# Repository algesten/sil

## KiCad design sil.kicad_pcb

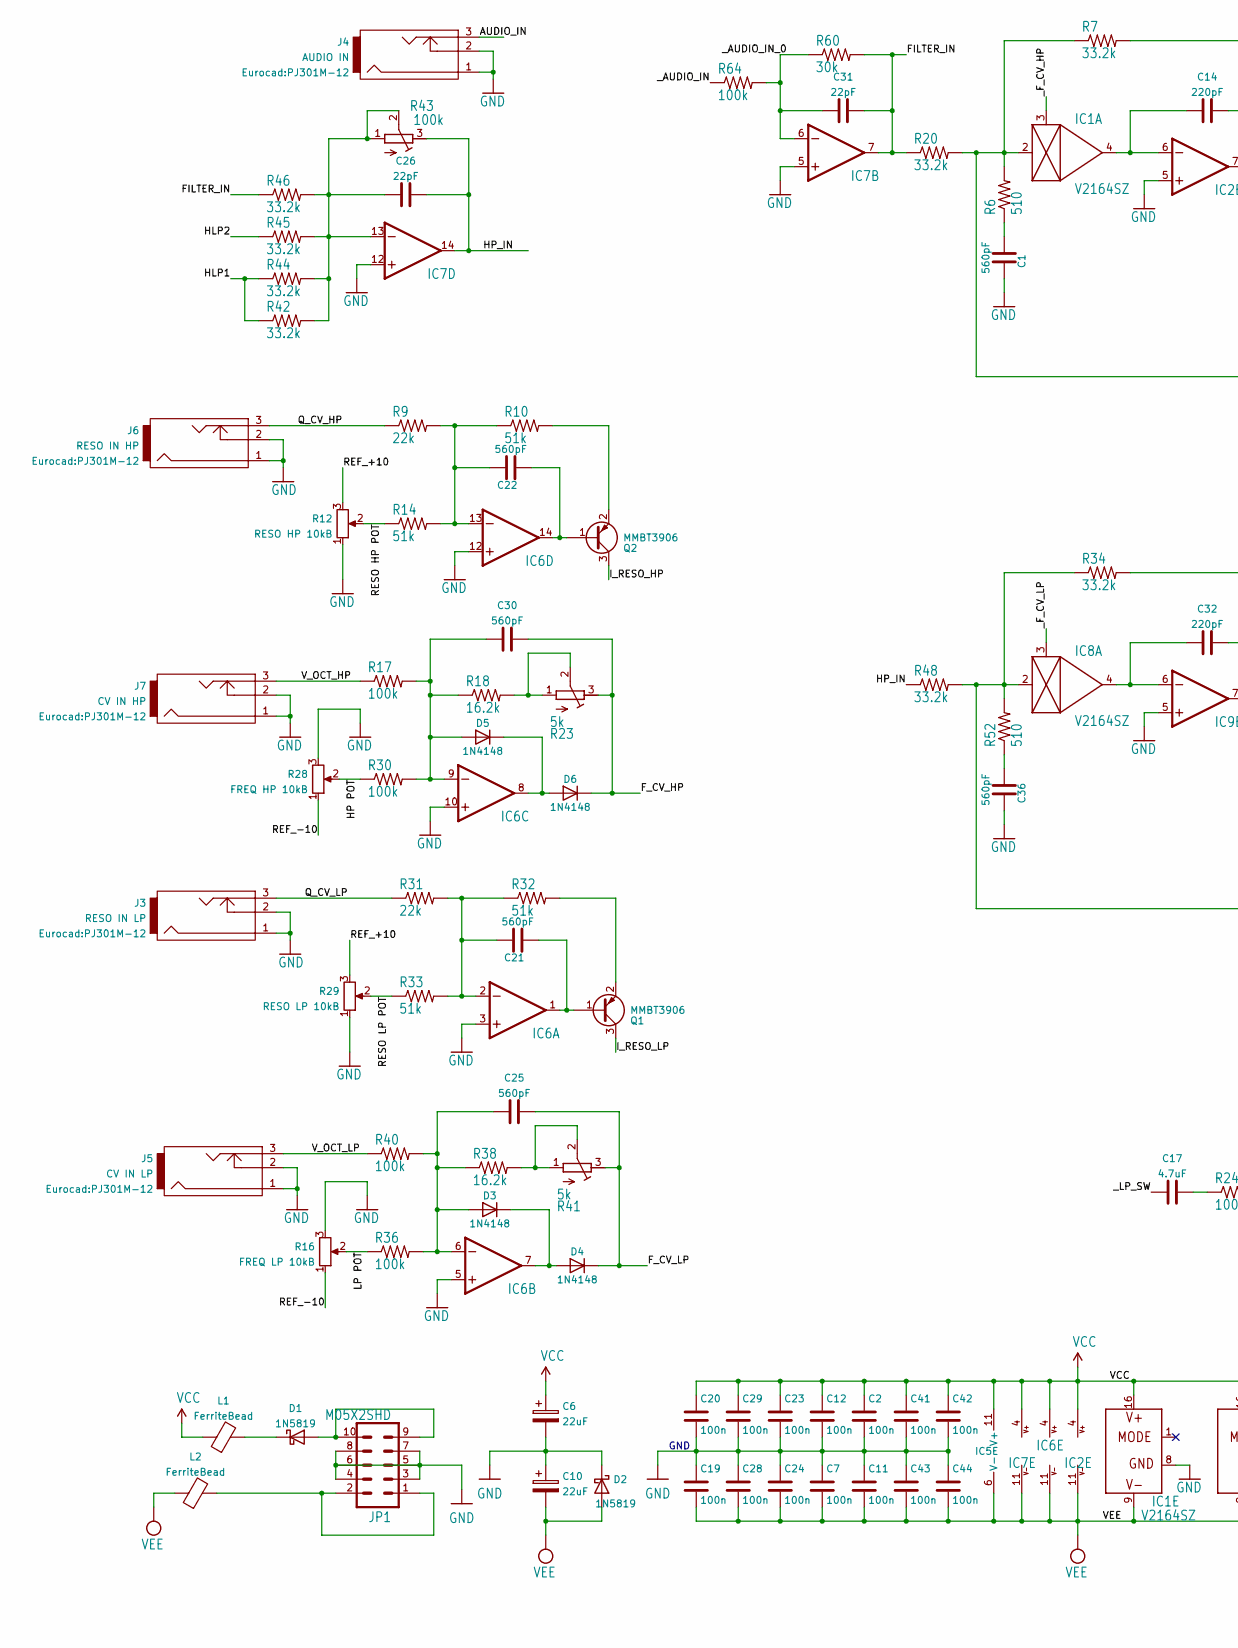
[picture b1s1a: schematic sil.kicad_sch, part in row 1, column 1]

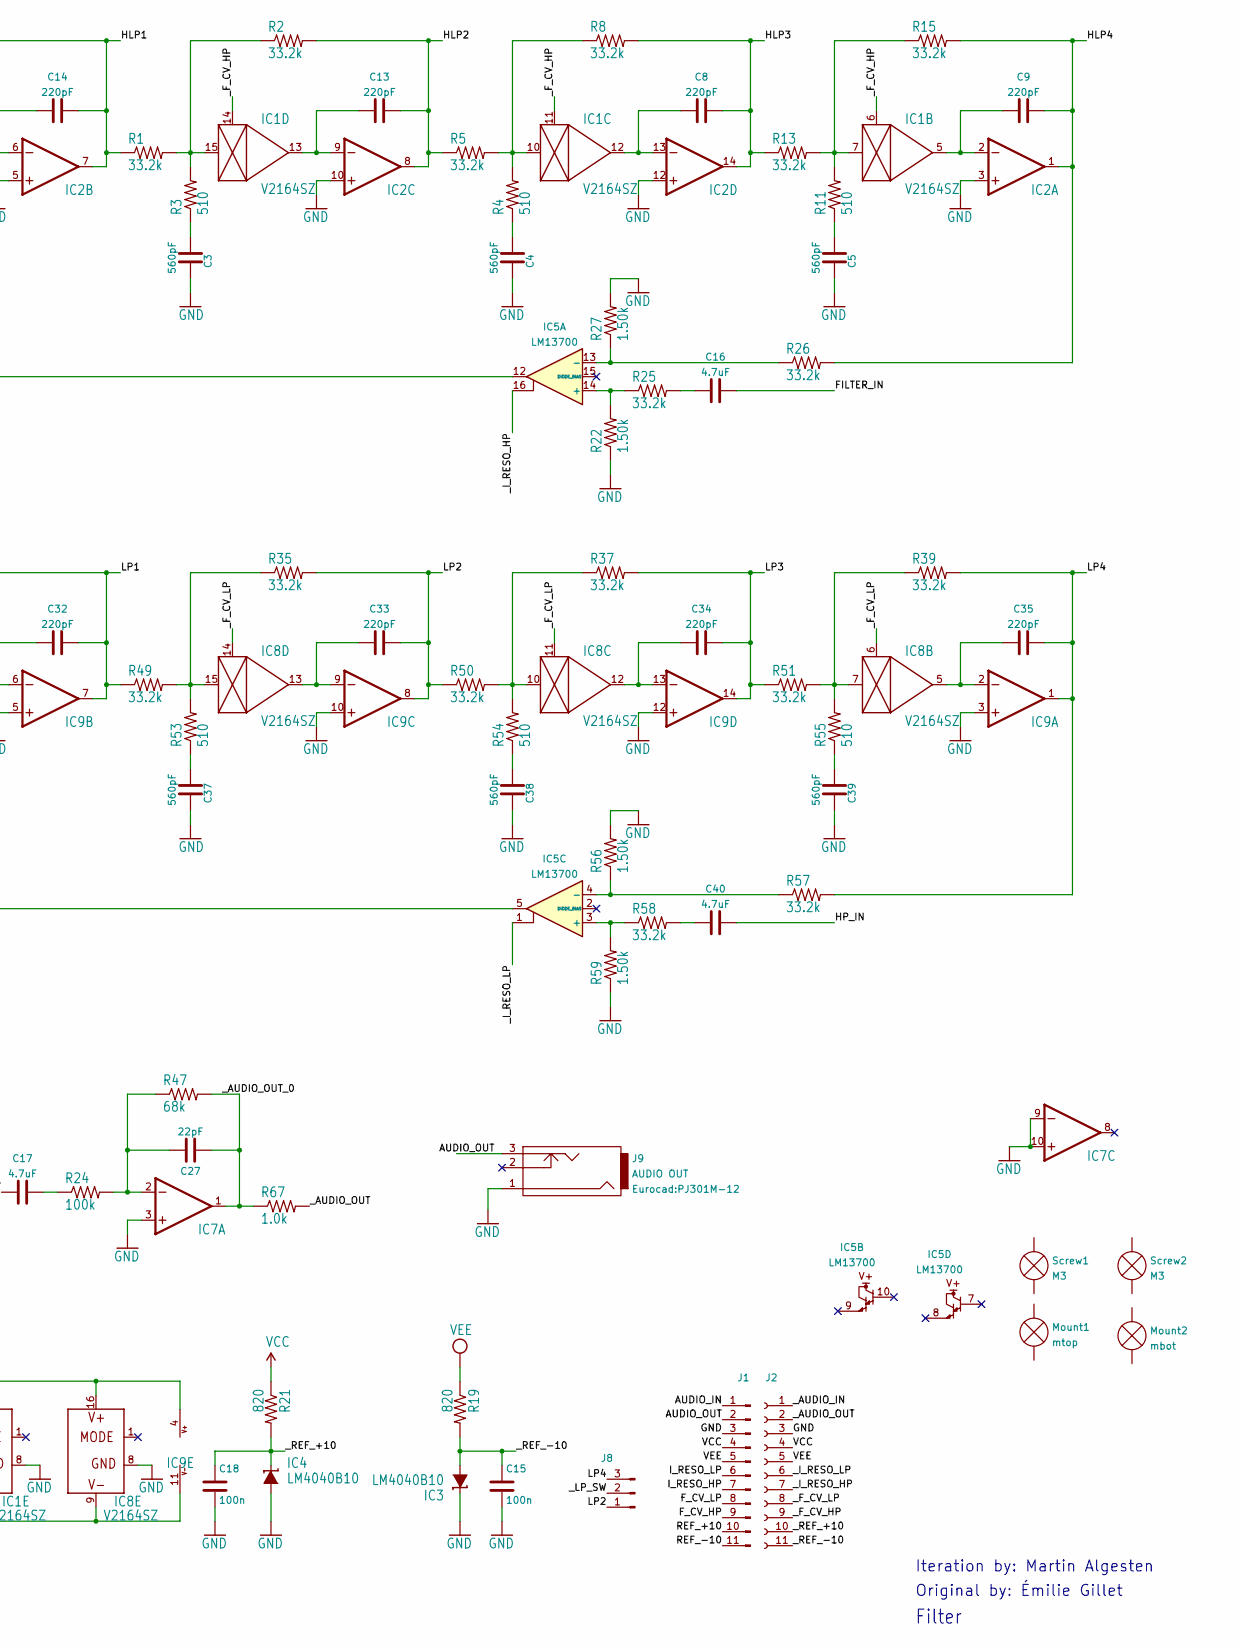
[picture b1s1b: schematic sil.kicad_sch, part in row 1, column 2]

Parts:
C1, C3, C4, C5, C21, C22, C25, C30, C36, C37, C38, C39: 560pF; C_0402_1005Metric; LCSC C318606
C2, C7, C11, C12, C15, C18, C19, C20, C23, C24, C28, C29, C41, C42, C43, C44: 100n; C_0402_1005Metric; LCSC C105882
C6, C10: 22uF; CP_Elec_5x5.4; LCSC C239256
C8, C9, C13, C14, C32, C33, C34, C35: 220pF; R_0603_1608Metric; LCSC C302060
C16, C40: 4.7uF; C_1206_3216Metric; LCSC C7237
C17: 4.7uF; R_1206_3216Metric; LCSC C318753
C26, C27, C31: 22pF; C_0402_1005Metric; LCSC C1555
D1, D2: 1N5819; D_SOD-123; LCSC C2905649
D3, D4, D5, D6: 1N4148; D_SOD-523; LCSC C68948
IC1, IC8: V2164SZ; SOIC-16_4.55x10.3mm_P1.27mm
IC2, IC7, IC9: OPA1679; TSSOP-14_4.4x5mm_P0.65mm
IC3, IC4: LM4040B10; SOT-23; LCSC C201738
IC5: LM13700; SOIC-16_3.9x9.9mm_P1.27mm
IC6: TL074; TSSOP-14_4.4x5mm_P0.65mm
J1: Conn_01x11_Male; PinHeader_1x11_P2.54mm_Vertical
J2: Conn_01x08_Female; PinSocket_1x11_P2.54mm_Vertical
J3: RESO IN LP; PJ301M-12
J4: AUDIO IN; PJ301M-12
J5: CV IN LP; PJ301M-12
J6: RESO IN HP; PJ301M-12
J7: CV IN HP; PJ301M-12
J8: Conn_01x03_Male; PinHeader_1x03_P2.54mm_Vertical
J9: AUDIO OUT; PJ301M-12
JP1: M05X2SHD; Power_small
L1, L2: FerriteBead; R_0402_1005Metric; LCSC C76883
Mount1: mtop; Mounting hole
Mount2: mbot; Mounting hole
Q1, Q2: MMBT3906; SOT-523; LCSC C2828444
R1, R2, R5, R7, R8, R13, R15, R20, R25, R26, R34, R35, R37, R39, R42, R44, R45, R46, R48, R49, R50, R51, R57, R58: 33.2k; R_0402_1005Metric; LCSC C2692992
R3, R4, R6, R11, R52, R53, R54, R55: 510; R_0402_1005Metric; LCSC C25123
R9, R31: 22k; R_0402_1005Metric; LCSC C25768
R10, R14, R32, R33: 51k; R_0402_1005Metric; LCSC C25794
R12: RESO HP 10kB; Alpha9mmPot
R16: FREQ LP 10kB; Alpha9mmPot
R17, R24, R30, R36, R40, R64: 100k; R_0402_1005Metric; LCSC C25741
R18, R38: 16.2k; R_0402_1005Metric; LCSC C27176
R19, R21: 820; R_0402_1005Metric; LCSC C227240
R22, R27, R56, R59: 1.50k; R_0402_1005Metric; LCSC C2692761
R23, R41: 5k; bourns trimpot
R28: FREQ HP 10kB; Alpha9mmPot
R29: RESO LP 10kB; Alpha9mmPot
R43: 100k; bourns trimpot
R47: 68k; R_0402_1005Metric; LCSC C36871
R60: 30k; R_0402_1005Metric; LCSC C25776
R67: 1.0k; R_0603_1608Metric; LCSC C21190
Screw1, Screw2: M3; M3 Screw

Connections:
/AUDIO_IN: J1.1, J4.3
/AUDIO_OUT: J1.2, J9.3
/FILTER_IN: C16.2, C31.2, IC7.7 (OUT), R20.1, R46.1, R60.2
/F_CV_HP: C30.2, D6.1 (K), J1.9, R23.3 (A)
/F_CV_LP: C25.2, D4.1 (K), J1.8, R41.3 (A)
/HLP1: C14.2, IC2.7 (OUT), R1.1, R7.2, R42.1, R44.1
/HLP2: C13.2, IC2.8 (OUT), R2.2, R5.1, R45.1
/HLP3: C8.2, IC2.14 (OUT), R8.2, R13.1
/HLP4: C9.2, IC2.1 (OUT), R15.2, R26.2
/HP POT: R28.2, R30.1
/HP_IN: C26.2, C40.2, IC7.14 (OUT), R43.3 (A), R48.1
/I_RESO_HP: J1.7, Q2.3 (C)
/I_RESO_LP: J1.6, Q1.3 (C)
/LP1: C32.2, IC9.7 (OUT), R34.2, R49.1
/LP2: C33.2, IC9.8 (OUT), J8.1, R35.2, R50.1
/LP3: C34.2, IC9.14 (OUT), R37.2, R51.1
/LP4: C35.2, IC9.1 (OUT), J8.3, R39.2, R57.2
/LP POT: R16.2, R36.1
/Q_CV_HP: J6.3, R9.1
/Q_CV_LP: J3.3, R31.1
/REF_+10: J1.10, R12.3, R29.3
/REF_-10: J1.11, R16.1, R28.1
/RESO HP POT: R12.2, R14.1
/RESO LP POT: R29.2, R33.1
/V_OCT_HP: J7.3, R17.1
/V_OCT_LP: J5.3, R40.1
/_AUDIO_IN: J2.1, R64.1
/_AUDIO_IN_0: C31.1, IC7.6 (-IN), R60.1, R64.2
/_AUDIO_OUT: J2.2, R67.2
/_AUDIO_OUT_0: C27.2, IC7.1 (OUT), R47.2, R67.1
/_F_CV_HP: IC1.3 (CTRL), IC1.6 (CTRL), IC1.11 (CTRL), IC1.14 (CTRL), J2.9
/_F_CV_LP: IC8.3 (CTRL), IC8.6 (CTRL), IC8.11 (CTRL), IC8.14 (CTRL), J2.8
/_I_RESO_HP: IC5.16, J2.7
/_I_RESO_LP: IC5.1, J2.6
/_LP_SW: C17.1, J8.2
/_REF_+10: C18.1, IC4.1 (C), J2.10, R21.2
/_REF_-10: C15.1, IC3.2 (A), J2.11, R19.2
GND: C1.2, C2.2, C3.2, C4.2, C5.2, C6.2, C7.1, C10.1, C11.1, C12.2, C15.2, C18.2, C19.1, C20.2, C23.2, C24.1, C28.1, C29.2, C36.2, C37.2, C38.2, C39.2, C41.2, C42.2, C43.1, C44.1, D2.1 (K), IC1.8 (GND), IC2.3 (+IN), IC2.5 (+IN), IC2.10 (+IN), IC2.12 (+IN), IC3.1 (C), IC4.2 (A), IC6.3 (+IN), IC6.5 (+IN), IC6.10 (+IN), IC6.12 (+IN), IC7.3 (+IN), IC7.5 (+IN), IC7.9 (-IN), IC7.10 (+IN), IC7.12 (+IN), IC8.8 (GND), IC9.3 (+IN), IC9.5 (+IN), IC9.10 (+IN), IC9.12 (+IN), J1.3, J2.3, J3.1, J3.2, J4.1, J4.2, J5.1, J5.2, J6.1, J6.2, J7.1, J7.2, J9.1, JP1.3, JP1.4, JP1.5, JP1.6, JP1.7, JP1.8, R12.1, R16.3, R22.1, R27.2, R28.3, R29.1, R56.2, R59.1
unnamed: C1.1, R6.1
unnamed: C3.1, R3.1
unnamed: C4.1, R4.1
unnamed: C5.1, R11.1
unnamed: C8.1, IC1.12 (OUT), IC2.13 (-IN)
unnamed: C9.1, IC1.5 (OUT), IC2.2 (-IN)
unnamed: C13.1, IC1.13 (OUT), IC2.9 (-IN)
unnamed: C14.1, IC1.4 (OUT), IC2.6 (-IN)
unnamed: C16.1, R25.2
unnamed: C17.2, R24.1
unnamed: C21.1, IC6.1 (OUT), Q1.1 (B)
unnamed: C21.2, IC6.2 (-IN), R31.2, R32.1, R33.2
unnamed: C22.1, IC6.14 (OUT), Q2.1 (B)
unnamed: C22.2, IC6.13 (-IN), R9.2, R10.1, R14.2
unnamed: C25.1, D3.2 (A), IC6.6 (-IN), R36.2, R38.1, R40.2
unnamed: C26.1, IC7.13 (-IN), R42.2, R43.1 (E), R43.2 (S), R44.2, R45.2, R46.2
unnamed: C27.1, IC7.2 (-IN), R24.2, R47.1
unnamed: C30.1, D5.2 (A), IC6.9 (-IN), R17.2, R18.1, R30.2
unnamed: C32.1, IC8.4 (OUT), IC9.6 (-IN)
unnamed: C33.1, IC8.13 (OUT), IC9.9 (-IN)
unnamed: C34.1, IC8.12 (OUT), IC9.13 (-IN)
unnamed: C35.1, IC8.5 (OUT), IC9.2 (-IN)
unnamed: C36.1, R52.1
unnamed: C37.1, R53.1
unnamed: C38.1, R54.1
unnamed: C39.1, R55.1
unnamed: C40.1, R58.2
unnamed: D1.1 (K), L1.2
unnamed: D1.2 (A), JP1.9, JP1.10
unnamed: D3.1 (K), D4.2 (A), IC6.7 (OUT)
unnamed: D5.1 (K), D6.2 (A), IC6.8 (OUT)
unnamed: IC1.2 (IN), IC5.12, R6.2, R7.1, R20.2
unnamed: IC1.7 (IN), R11.2, R13.2, R15.1
unnamed: IC1.10 (IN), R4.2, R5.2, R8.1
unnamed: IC1.15 (IN), R1.2, R2.1, R3.2
unnamed: IC5.3 (+), R58.1, R59.2
unnamed: IC5.4 (-), R56.1, R57.1
unnamed: IC5.5, IC8.2 (IN), R34.1, R48.2, R52.2
unnamed: IC5.13 (-), R26.1, R27.1
unnamed: IC5.14 (+), R22.2, R25.1
unnamed: IC8.7 (IN), R39.1, R51.2, R55.2
unnamed: IC8.10 (IN), R37.1, R50.2, R54.2
unnamed: IC8.15 (IN), R35.1, R49.2, R53.2
unnamed: JP1.1, JP1.2, L2.2
unnamed: Q1.2 (E), R32.2
unnamed: Q2.2 (E), R10.2
unnamed: R18.2, R23.1 (E), R23.2 (S)
unnamed: R38.2, R41.1 (E), R41.2 (S)
VCC: C2.1, C6.1, C12.1, C20.1, C23.1, C29.1, C41.1, C42.1, IC1.16 (V+), IC2.4 (V+), IC5.11 (V+), IC6.4 (V+), IC7.4 (V+), IC8.16 (V+), IC9.4 (V+), J1.4, J2.4, L1.1, R21.1
VEE: C7.2, C10.2, C11.2, C19.2, C24.2, C28.2, C43.2, C44.2, D2.2 (A), IC1.9 (V-), IC2.11 (V-), IC5.6 (V-), IC6.11 (V-), IC7.11 (V-), IC8.9 (V-), IC9.11 (V-), J1.5, J2.5, L2.1, R19.1

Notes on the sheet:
Filter
Original by: Émilie Gillet
Iteration by: Martin Algesten
GND

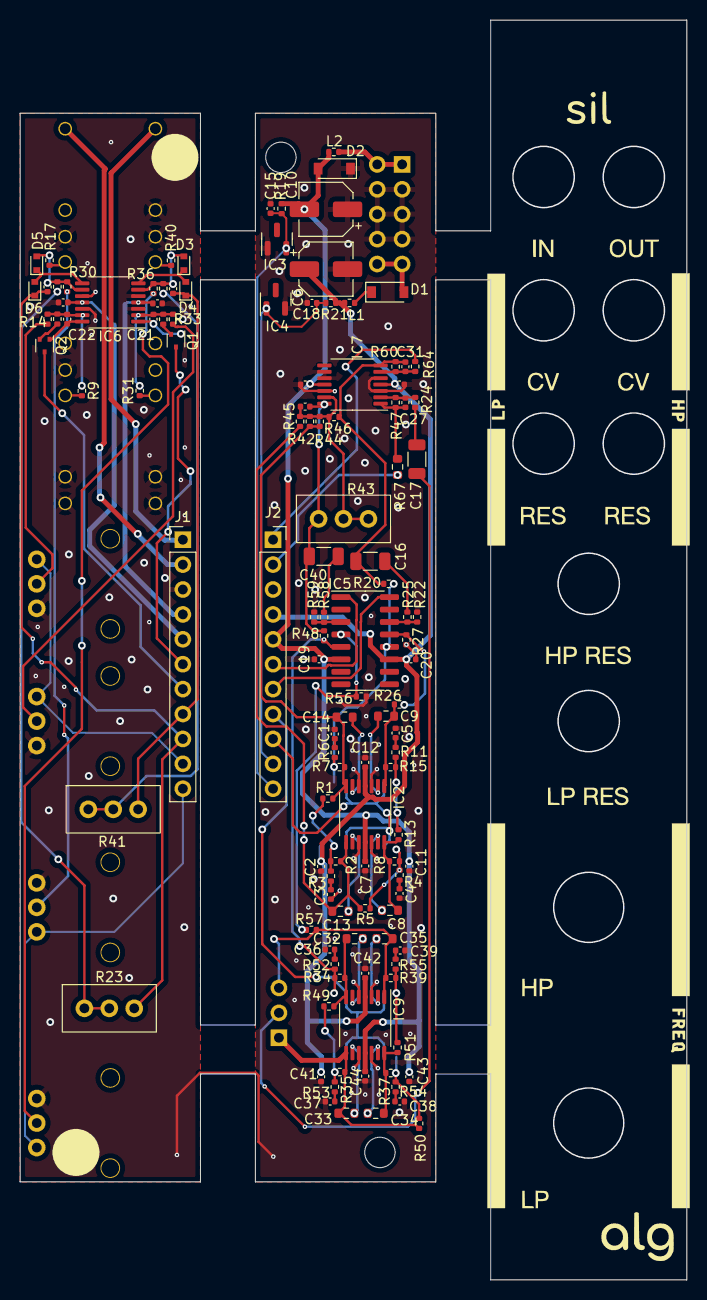
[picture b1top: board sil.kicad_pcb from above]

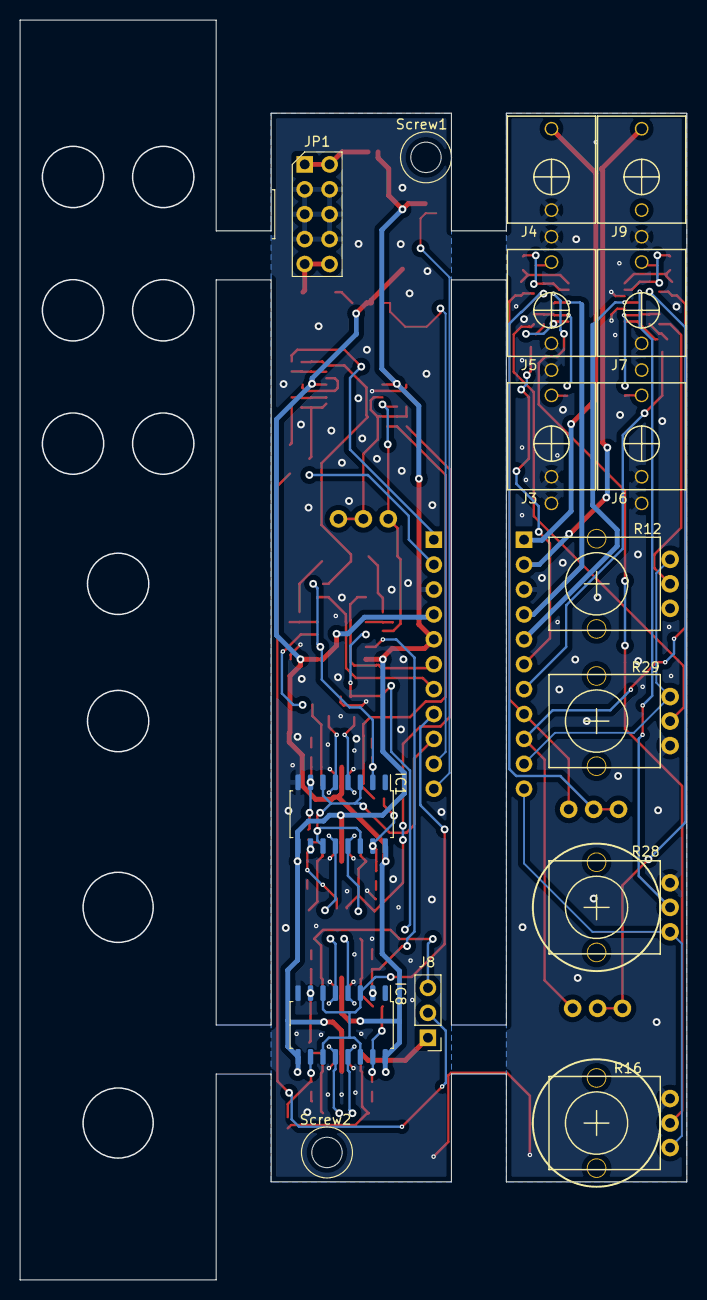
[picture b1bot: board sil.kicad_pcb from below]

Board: 2 copper layers, 68.0 x 128.5 mm, 139 parts (16 on the bottom side), 88 nets.
